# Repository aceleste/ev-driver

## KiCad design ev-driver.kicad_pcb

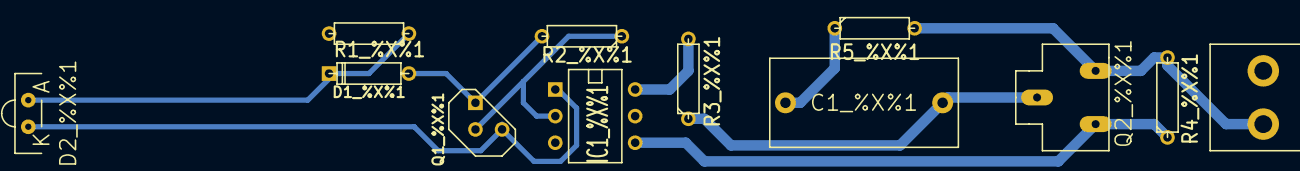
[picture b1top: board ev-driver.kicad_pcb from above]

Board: 2 copper layers, 12 parts (0 on the bottom side), 9 nets.

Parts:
C1_%X%1: 0.1uF; C_Radial_15mm
D1_%X%1: 1N4002; D3
D2_%X%1: LED; LED_ThroughHole_SideView
IC1_%X%1: MOC3042M; DIP-6__300
P1_%X%1: CONN_01X02; Bornier_1x02_5.08mm
Q1_%X%1: BC237; TO92-EBC
Q2_%X%1: TRIAC_BTA2; TO-227-Socket
R1_%X%1: 240R; R3
R2_%X%1, R5_%X%1: 47R; R3
R3_%X%1: 360R; R3
R4_%X%1: 330R; R3

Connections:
/ctrl_input_common: D1_%X%1.1, Q1_%X%1.E, R2_%X%1.2
/load_output_p_%X%: P1_%X%1.1, Q2_%X%1.1, R4_%X%1.2, R5_%X%1.2
/main_p_common: C1_%X%1.1, Q2_%X%1.2, R3_%X%1.1
unnamed: C1_%X%1.2, R5_%X%1.1
unnamed: D1_%X%1.2, D2_%X%1.1, R1_%X%1.1
unnamed: D2_%X%1.2, IC1_%X%1.1, Q1_%X%1.C
unnamed: IC1_%X%1.2, Q1_%X%1.B, R2_%X%1.1
unnamed: IC1_%X%1.4, Q2_%X%1.3, R4_%X%1.1
unnamed: IC1_%X%1.6, R3_%X%1.2

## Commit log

2014-12-01 Pre-branch commit
